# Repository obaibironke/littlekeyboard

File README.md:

# littlekeyboard
My own version of the hackpad from Hack Club

BOM:
6x Switches
1X Seeed Studio Xiao Rp2040
1X 0.91" OLED Screen
1X EC11 Rotary Encoder
2X SK6812 MINI-E RGB LED
1X Case (2 Printed Parts)
4X M3x16mm screws
4X M3x5mx4mm heatset inserts
6X Keycaps

Overall hackpad:

Schematic:

PCB:

Render:

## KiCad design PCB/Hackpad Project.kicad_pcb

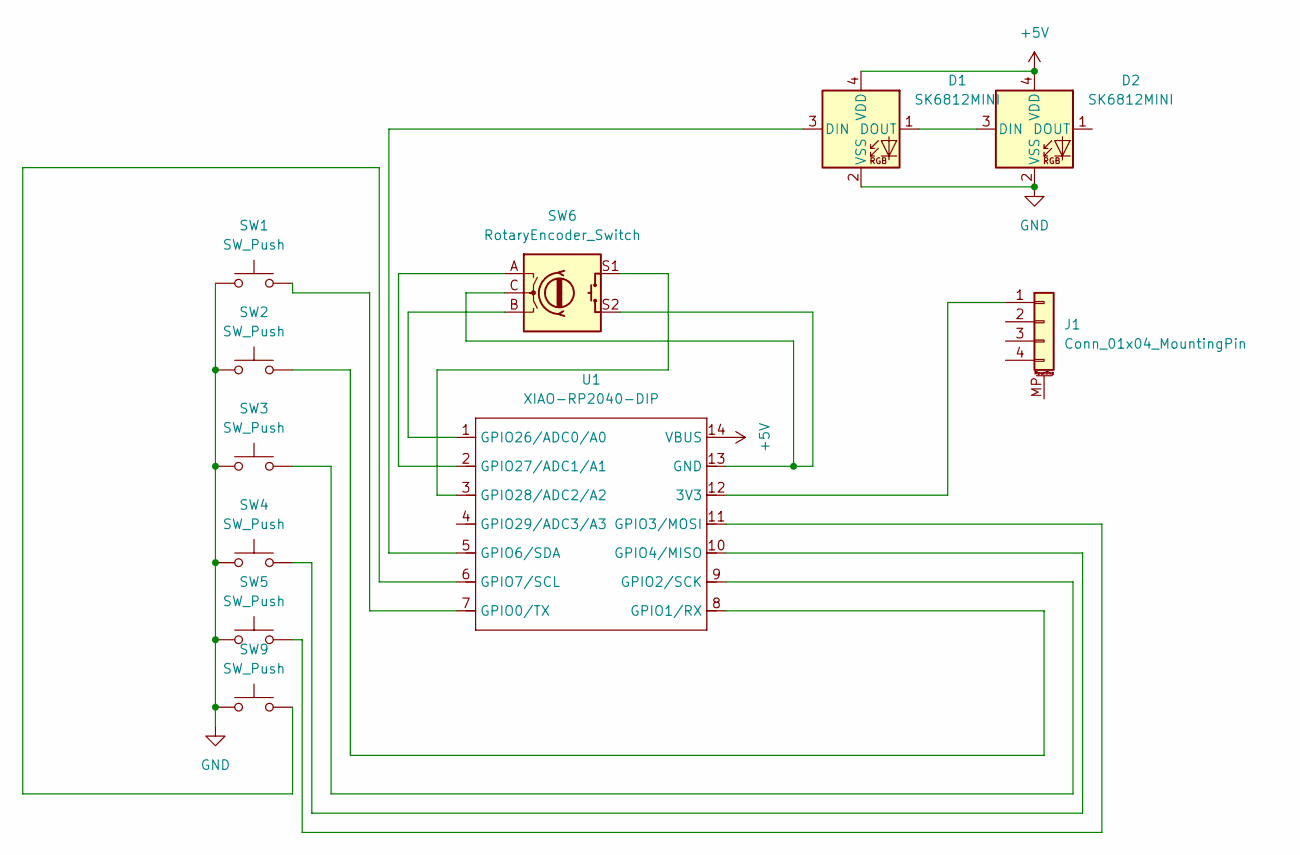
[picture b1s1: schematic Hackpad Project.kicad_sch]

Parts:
D1, D2: SK6812MINI; LED_SK6812MINI_PLCC4_3.5x3.5mm_P1.75mm
J1: Conn_01x04_MountingPin; SSD1306-0.91-OLED-4pin-128x32
SW1, SW2, SW3, SW4, SW5, SW9: SW_Push; SW_Cherry_MX_1.00u_PCB
SW6: RotaryEncoder_Switch; RotaryEncoder_Alps_EC11E-Switch_Vertical_H20mm
U1: XIAO-RP2040-DIP

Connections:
+5V: D1.4 (VDD), D2.4 (VDD), U1.14 (VBUS)
GND: D1.2 (VSS), D2.2 (VSS), SW1.1, SW2.1, SW3.1, SW4.1, SW5.1, SW9.1
unnamed: D1.3 (DIN), U1.5 (GPIO6/SDA)
unnamed: D1.1 (DOUT), D2.3 (DIN)
unnamed: J1.1, U1.12 (3V3)
unnamed: SW6.C, SW6.S2, U1.13 (GND)
unnamed: SW1.2, U1.7 (GPIO0/TX)
unnamed: SW2.2, U1.8 (GPIO1/RX)
unnamed: SW3.2, U1.9 (GPIO2/SCK)
unnamed: SW5.2, U1.11 (GPIO3/MOSI)
unnamed: SW4.2, U1.10 (GPIO4/MISO)
unnamed: SW9.2, U1.6 (GPIO7/SCL)
unnamed: SW6.B, U1.1 (GPIO26/ADC0/A0)
unnamed: SW6.A, U1.2 (GPIO27/ADC1/A1)
unnamed: SW6.S1, U1.3 (GPIO28/ADC2/A2)

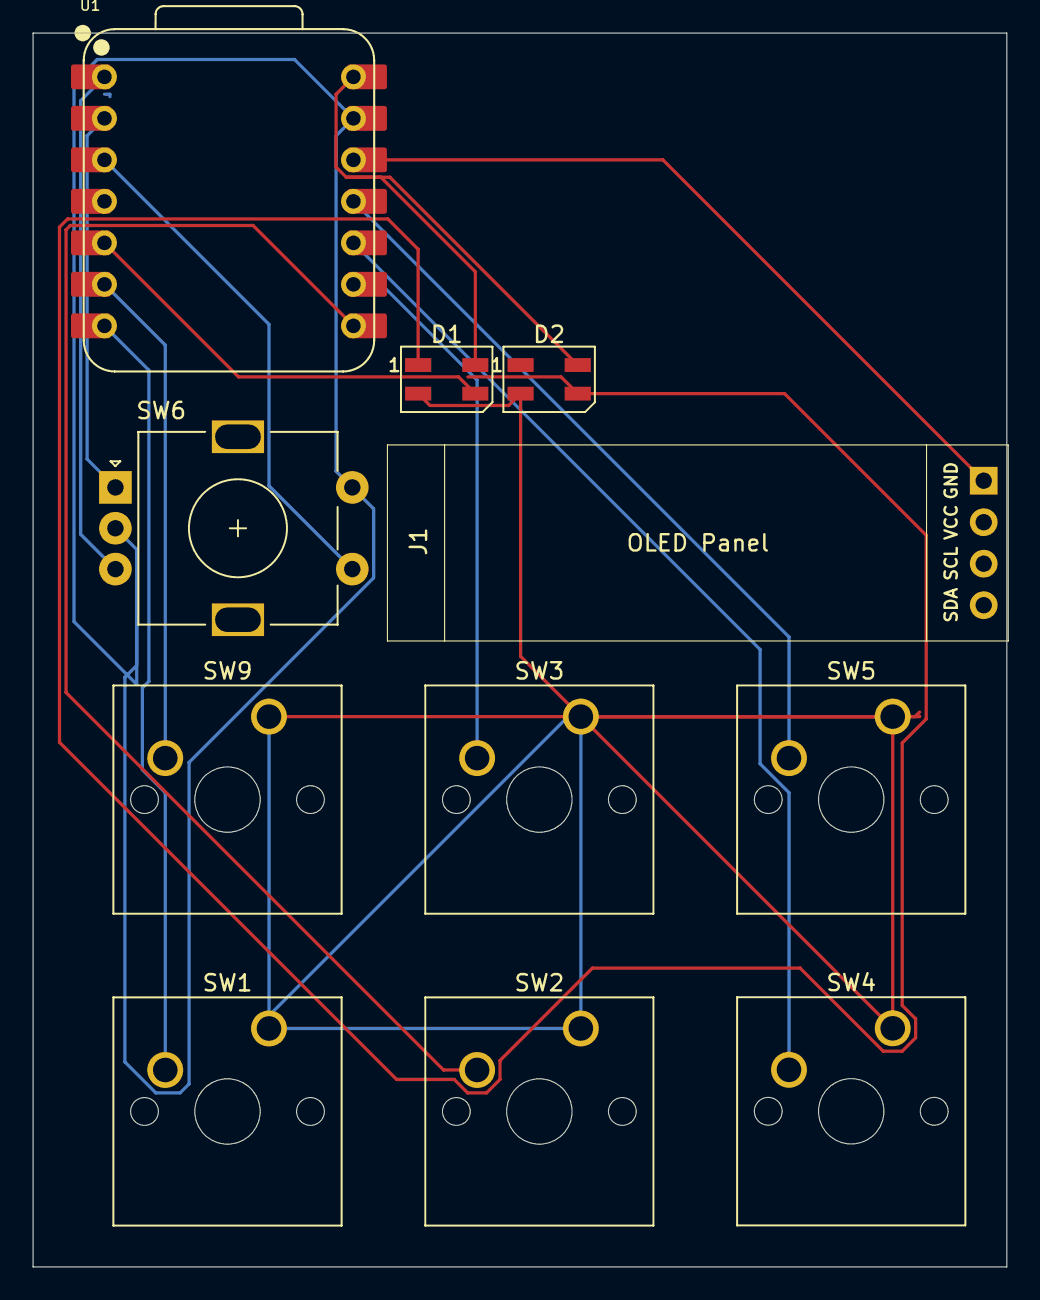
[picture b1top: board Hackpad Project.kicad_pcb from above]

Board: 2 copper layers, 59.6 x 75.5 mm, 11 parts (0 on the bottom side), 15 nets.
